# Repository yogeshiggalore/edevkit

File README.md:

# edevkit

> Open-source **embedded developer kits** for ARM + RISC-V work — one
> board on your desk that replaces a drawer full of dongles.

**edevkit** is a family of single-board USB-powered developer kits. Each
unit folds a debug probe, a stack of protocol testers, and a host
GUI / CLI into one device, so a developer working on an embedded board
can flash, debug, log, sniff, drive, emulate, and bring up new firmware
without keeping six other tools on the bench.

A single edevkit unit gives you, in one USB-C cable's worth of wiring:

- **ARM + RISC-V debug probe** — CMSIS-DAP v2 over USB, SWD + JTAG,
  works with pyOCD / OpenOCD / probe-rs / GDB
- **SWO trace capture** — ITM/TPIU output decoded and streamed to host
- **Two UART bridges** — one for the target's log console, one for
  developer-driven protocol testing (independent voltage domains)
- **I²C protocol tester** — master, slave, or sniffer at any address,
  up to 3.4 MHz
- **SPI / DSPI / QSPI tester** — master / slave / sniffer in every
  CPHA/CPOL mode, up to 50 MHz QSPI master
- **Device emulation engine** — YAML-driven; plays the role of a real
  SPI flash chip / I²C sensor / UART AT-modem so you can develop the
  *host* side without the actual peripheral on hand
- **OTA firmware updates** for the kit itself — MCUboot + SMP, no
  unplugging
- **Host stack** — a Tauri desktop GUI for visual inspection plus a
  Rust CLI for scripting and CI

The current product is **edevkit1**, in design (RP2350B Cortex-M33,
Zephyr 4.x, MCUboot). Future generations (`edevkit2`, …) will share
this same repo, toolchain, host stack, and docs hub — only the
hardware-specific design doc gets a version-numbered name.

---

## I'm new here — where do I start?

**Open the installation guide directly in your browser.** It's a
self-contained HTML page — no server, no build step, no setup required.

```bash
git clone https://github.com/yogeshiggalore/edevkit.git
cd edevkit

# macOS:
open tools/web/pages/installation.html

# Linux:
xdg-open tools/web/pages/installation.html

# Windows (PowerShell):
start tools/web/pages/installation.html
```

Or just double-click the file in your file manager. The same applies to
every other doc under `tools/web/pages/` — they're all standalone HTML
with embedded CSS, browseable via `file://` without any tooling.

The install guide walks you through (cross-platform):

1. System prerequisites (cmake, ninja, gperf, dtc, …)
2. Cloning the repo
3. Python venv + `west`
4. Zephyr workspace
5. Zephyr SDK
6. RP2350 PIO assembler
7. Rust + Tauri (host)
8. KiCad 9 + KiBot (hardware)
9. Enclosure CAD (CadQuery / FreeCAD)
10. Slicer (OrcaSlicer)
11. Bench tools (sigrok, mcumgr, serial)
12. Editor / IDE setup
13. Shell helpers
14. Smoke tests
15. Final checklist

Estimated total time: **1.5–3 hours** (mostly unattended downloads).

---

## I'm already set up — give me the docs hub

Once your venv is active, run the local docs hub for searchable
cross-referenced docs (light/dark theme, keyboard shortcuts, auto-discovers
new pages):

```bash
source "$EDEV_VENV/bin/activate"
cd tools/web
python server.py
# open http://127.0.0.1:8765/
```

The hub serves the same files you can already open via `file://` —
plus a searchable index, sidebar nav, and theme toggle.

---

## Repository layout

```
edevkit/
├── firmware/           Zephyr workspace + applications
│                       (per-product subdirs as the family grows)
├── hardware/           KiCad 9 schematic + PCB
├── host/               Rust workspace — Tauri GUI + CLI
├── enclosure/          CadQuery / FreeCAD source for 3D-printed shells
├── documents/          Non-HTML artifacts (PDFs, captures, diagrams)
└── tools/
    └── web/            Local docs hub (FastAPI)
        ├── pages/      ← all project HTML docs (open via file:// or hub)
        ├── server.py
        ├── static/     theme + JS
        └── templates/  Jinja2 templates
```

## Products

| Product   | Status     | Hardware                                  |
|-----------|------------|-------------------------------------------|
| edevkit1  | In design  | RP2350B (Cortex-M33) · Zephyr 4.x · MCUboot |

Future generations (edevkit2, …) will use this same repo, this same
toolchain, and these same docs hub conventions — only product-specific
content gets a version-numbered name.

## Documentation

All docs live under [`tools/web/pages/`](tools/web/pages/):

- [edevkit1 design spec](tools/web/pages/edevkit1.html) — v1 architecture (source of truth)
- [Installation guide](tools/web/pages/installation.html) — cross-platform onboarding

Drop any new `.html` into `tools/web/pages/` and it's immediately
discoverable by the docs hub (and openable via `file://`).

## Contributing

This is an open-hardware project: every contribution should be
reproducible from open-source tooling. No proprietary CAD, no
closed-source build steps. See the design spec's Decision Log section
for what's settled and what's still open.

## License

TBD.

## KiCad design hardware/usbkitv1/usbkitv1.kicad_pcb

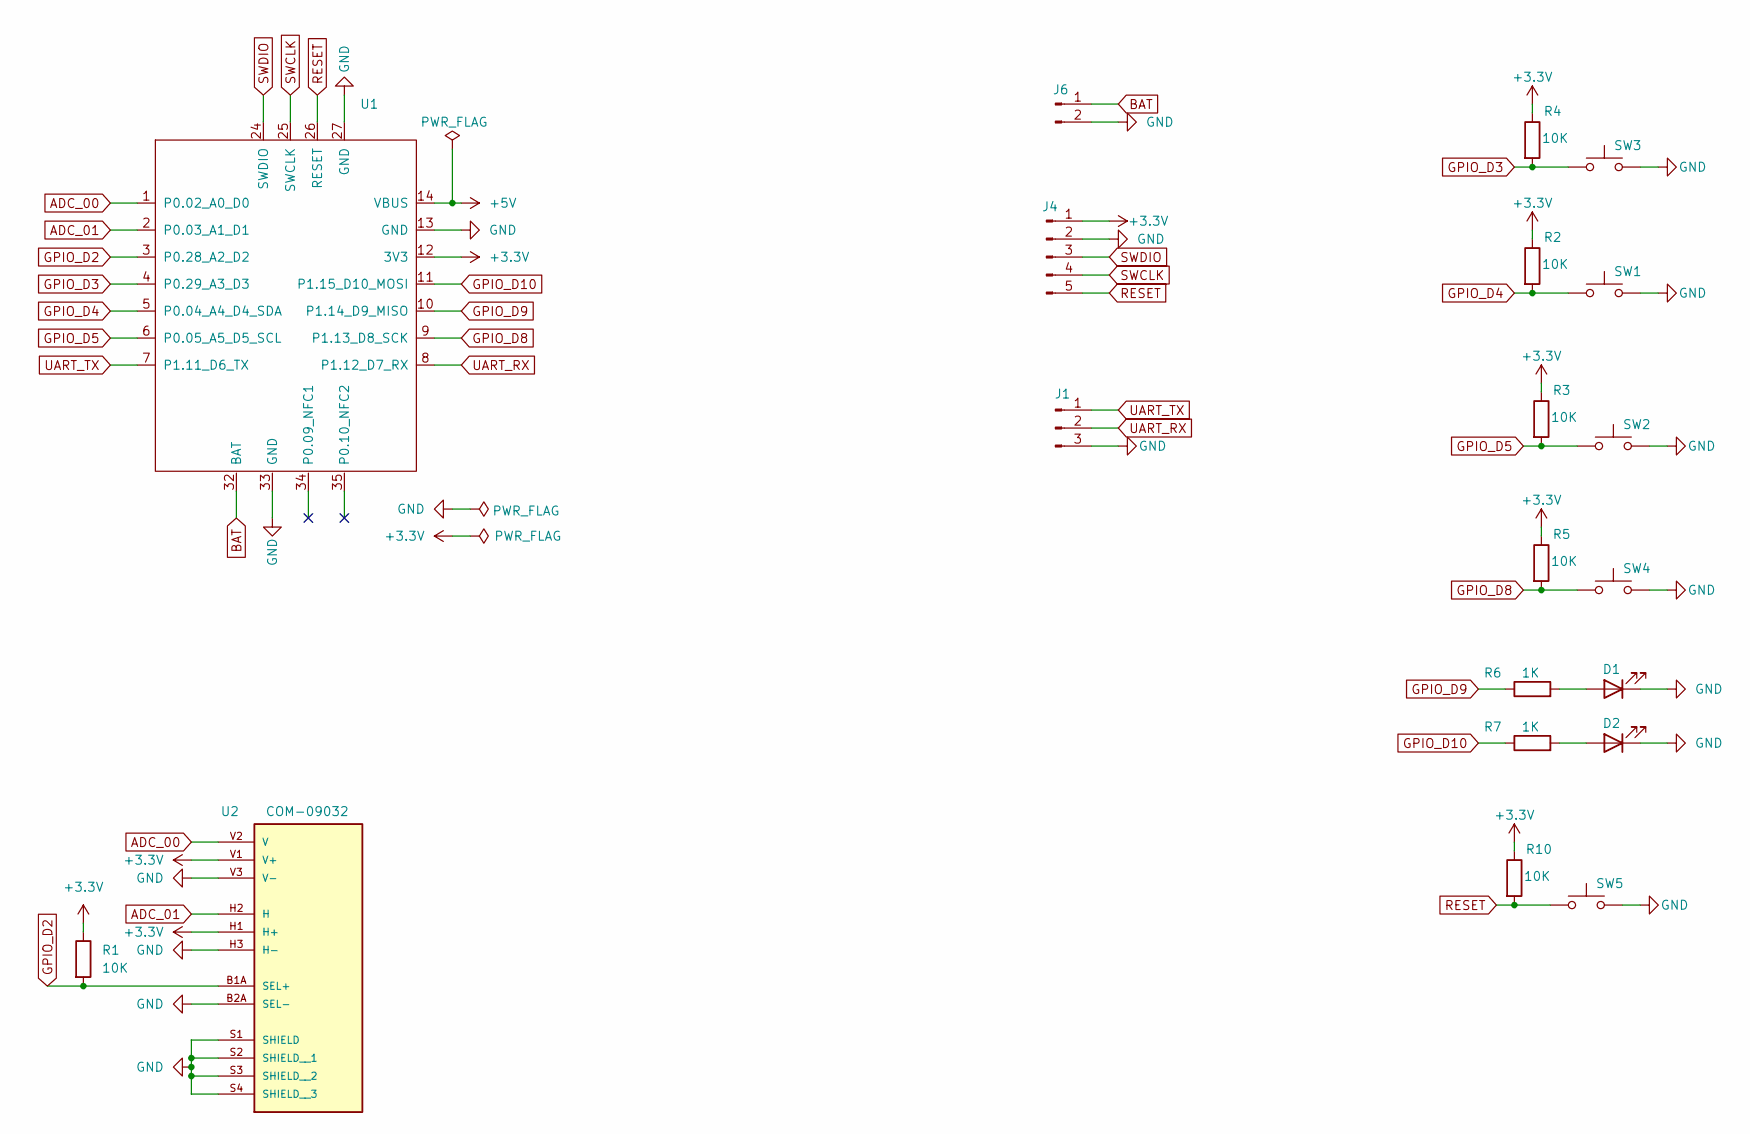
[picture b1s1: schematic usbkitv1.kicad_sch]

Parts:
D1, D2: LED; LED_0805_2012Metric_Pad1.15x1.40mm_HandSolder
J1: Conn_01x03_Pin; PinHeader_1x03_P2.54mm_Vertical
J4: Conn_01x05_Pin; PinHeader_1x05_P2.54mm_Vertical
J6: Conn_01x02_Pin; PinHeader_1x02_P2.54mm_Vertical
R1, R2, R3, R4, R5, R10: 10K; R_0805_2012Metric_Pad1.20x1.40mm_HandSolder
R6, R7: 1K; R_0805_2012Metric_Pad1.20x1.40mm_HandSolder
SW1, SW2, SW3, SW4: SW_Push; SW_PUSH-12mm
SW5: SW_Push; SW_PUSH_6mm
U1: XIAO-nRF52840-SMD
U2: COM-09032; XDCR_COM-09032; PARTREV N/A

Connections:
+3.3V: J4.1, R1.1, R2.1, R3.1, R4.1, R5.1, R10.1, U1.12 (3V3), U2.H1 (H+), U2.V1 (V+)
+5V: U1.14 (VBUS)
ADC_00: U1.1 (P0.02_A0_D0), U2.V2 (V)
ADC_01: U1.2 (P0.03_A1_D1), U2.H2 (H)
BAT: J6.1, U1.32 (BAT)
GND: D1.1 (K), D2.1 (K), J1.3, J4.2, J6.2, SW1.2, SW2.2, SW3.2, SW4.2, SW5.2, U1.13 (GND), U1.27 (GND), U1.33 (GND), U2.B2A (SEL-), U2.H3 (H-), U2.S1 (SHIELD), U2.S2 (SHIELD__1), U2.S3 (SHIELD__2), U2.S4 (SHIELD__3), U2.V3 (V-)
GPIO_D2: R1.2, U1.3 (P0.28_A2_D2), U2.B1A (SEL+)
GPIO_D3: R4.2, SW3.1, U1.4 (P0.29_A3_D3)
GPIO_D4: R2.2, SW1.1, U1.5 (P0.04_A4_D4_SDA)
GPIO_D5: R3.2, SW2.1, U1.6 (P0.05_A5_D5_SCL)
GPIO_D8: R5.2, SW4.1, U1.9 (P1.13_D8_SCK)
GPIO_D9: R6.1, U1.10 (P1.14_D9_MISO)
GPIO_D10: R7.1, U1.11 (P1.15_D10_MOSI)
unnamed: D1.2 (A), R6.2
unnamed: D2.2 (A), R7.2
RESET: J4.5, R10.2, SW5.1, U1.26 (RESET)
SWCLK: J4.4, U1.25 (SWCLK)
SWDIO: J4.3, U1.24 (SWDIO)
UART_RX: J1.2, U1.8 (P1.12_D7_RX)
UART_TX: J1.1, U1.7 (P1.11_D6_TX)

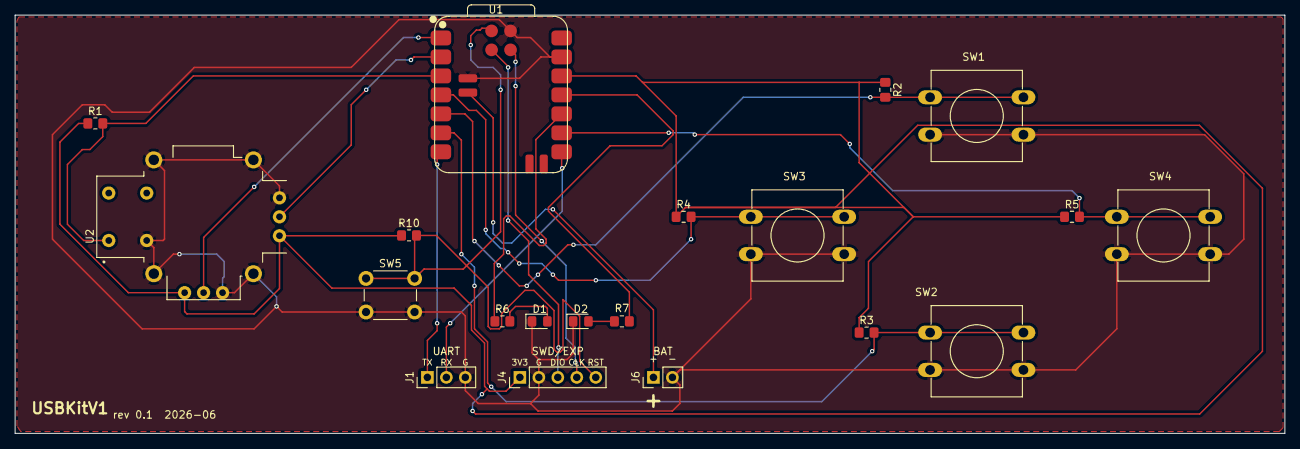
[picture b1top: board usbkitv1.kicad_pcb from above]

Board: 2 copper layers, 170.0 x 56.0 mm, 20 parts (0 on the bottom side), 19 nets.

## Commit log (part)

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2026-05-04 chore(docs): add Tailwind build tooling for the docs hub
    The docs hub at tools/web/ now uses Tailwind for ~95% of its styling.
    This commit lands the build setup so contributors can rebuild the CSS
    locally:
    - package.json: build:css / watch:css npm scripts
    - tailwind.config.js: brand palette, fonts, animations, content globs
    - tailwind.input.css: @tailwind directives + minimal custom layer
2026-05-04 feat(docs-hub): redesign hub — Tailwind, PWA, syntax highlight, search
    Rework tools/web/ from a hand-rolled CSS hub into a Tailwind-driven
    hub with full-text search, syntax highlighting, and offline support.
    Server (server.py):
    - Add 5 new categories — Architecture, USB stack, Debug, Protocols,
    Platform — slotted between Workflow and Bring-up so the chapter
    pages added in the next commit have homes
2026-05-04 docs: rewrite top-level README as the project's front door
    The previous README was a 2-line placeholder. Replace it with a
    proper landing page that introduces the edevkit family, summarizes
    what one unit does, and points new contributors to the docs hub.
    Highlights:
    - Frame "edevkit" as the umbrella brand and "edevkit1" as the
    current RP2350B product (consistent with the docs-hub naming)
2026-06-26 fix(edev_dapv2): nRF5340 flash via pyocd subprocess (Bug 2 — App side)
    probe-rs CMSIS-DAP flash silently fails on nRF5340: loader parses the HEX,
    exits without sending any flash transaction; misleading "TransferBlock
    USB timeout" message reported. Investigated via full RUST_LOG=trace —
    firmware ACKs every SWD transfer; the failure is host-side.
    Workaround: route nRF5340 hex through pyocd's FileProgrammer in a
    subprocess. Two issues blocked it:
2026-06-26 simplify(edev_dapv2 webgui): erase = wipe both cores + CTRL-AP reset
    The erase flow had grown three extra stages — UICR-disable stub upload,
    post-erase read-back verify, SYSRESETREQ-vs-CTRL-AP-reset switching for
    nRF5340 — that the user doesn't want. Strip them.
    Erase is now exactly:
    1. CTRL-AP#2 ERASEALL (App flash + App UICR)
    2. CTRL-AP#3 ERASEALL (Net flash + Net UICR, nRF5340 only)
2026-06-26 fix(edev_dapv2 webgui): pass --allow-erase-all on probe-rs read
    probe-rs reads a Nordic dual-core chip with a locked core hit
    "lacked the permission to do so: erase_all" because the auto-unlock
    path needs explicit permission. Trade-off documented at the call
    site: locked cores get auto-erased during read.
2026-06-26 feat(edev_dapv2 webgui): pyocd-based Net core flasher
    Direct host-driven Net flash via AP#1 + Net NVMC bridge, no on-target
    stub or SPU bootstrap needed:
    1. Defensive CTRL-AP#3 RESET pulse (clears any stuck-erase state from
    prior aborted ops)
    2. CTRL-AP#3 ERASEALL — wipes Net flash + Net UICR, unlocks Net AHB-AP
    for the rest of the session
2026-06-26 feat(edev_dapv2 webgui): J-Link CORESIGHT_Configure equivalent
    Ports nrfjprog's chip-recovery sequence into pure CMSIS-DAP. When the
    chip is in a stuck state — sticky CTRL/STAT errors, dormant DP, or a
    never-completing NVMC operation holding ERASEALLSTATUS at busy — our
    plain dp.connect() doesn't unstick it; J-Link does, and the magic
    turns out to live inside JLINK_CORESIGHT_Configure().
    New helper _full_dp_wake() runs the full ADIv5 §B5 init sequence via
2026-06-26 feat(edev_dapv2): permanent UICR.APPROTECT=HwDisabled after Net flash
    Hex files from production (Ring Pro 351) ship without UICR content.
    Without UICR.APPROTECT programmed to 0x50FA50FA (HwDisabled), the chip
    re-locks Net AHB-AP on every reset — so any post-reset readback verify
    returns garbage (the exact pattern we and nrfjprog both saw).
    Fix: after writing Net flash, while AHB-APs are still open from the
    CTRL-AP ERASEALL we did at the start of the session, program:
2026-06-26 fix(edev_dapv2 webgui): direct pyocd reads, no probe-rs auto-erase
    /api/read for nRF5340 was using probe-rs with --allow-erase-all.
    When ANY core was locked (typical post-reset state), probe-rs's
    Nordic vendor sequence would trigger a CTRL-AP ERASEALL — wiping
    BOTH cores, not just the locked one. Every readback verification
    was destroying the firmware we'd just programmed.
    Switch to direct pyocd AHB-AP reads for both App (AP#0, CSW=0x23000002)
2026-06-30 docs(esp32): add ESP32-S3 USB-host BLE bridge implementation guide
    The Pico 2 W stays as a pure USB CMSIS-DAP v2 probe; BLE moves to a
    separate ESP32-S3 firmware that hosts the probe over native USB-OTG
    and exposes its capabilities to a phone/fleet tool as semantic
    commands over BLE (NUS-style GATT + TLV framing).
    ESP32_BRIDGE.md is a complete implementation guide for that firmware
    — architecture, USB host code skeleton, NimBLE setup, TLV protocol,
2026-06-30 feat(edev_dapv2_zephyr): nRF5340 step 1 — DP/AP primitives + algorithm doc
    Lay the foundation for porting the canonical nRF5340 recover / erase /
    write / read flow from the pico-sdk Python webgui (feat/edev_dapv2 branch,
    algorithm-only reference) into the Zephyr probe firmware. The Pico runs
    the multi-step CTRL-AP / NVMC / UICR / stub-upload sequence itself; host
    orchestration becomes thin (one DAP vendor command per high-level op).
    Adds:
2026-06-30 feat(edev_dapv2_zephyr): nRF5340 step 3 — App UICR programming (cmd 0x8A)
    Implements the host-side App UICR.APPROTECT / SECUREAPPROTECT
    programming flow — no on-target stub needed because the App core's
    secure context is set up by silicon defaults. Net core UICR needs the
    SPU bootstrap stub (step 4). Algorithm: docs/NRF5340_ALGORITHMS.md §4
    Stage 3.
    Adds:
2026-06-30 feat(edev_dapv2_zephyr): nRF5340 step 4 — Net stub + UICR programming (cmd 0x8B)
    Implements the on-target Net-core stub path for permanently disabling
    APPROTECT on the network core. Required because nRF5340 Net peripherals
    are "Selectable Secure" and bare Secure-mode AHB-AP writes fault until
    the SPU is configured — sidestepped by running the programming code on
    the Net CPU itself, where silicon defaults give us the secure context
    we need. Algorithm: docs/NRF5340_ALGORITHMS.md §4 Stages 4–8 + §7.
2026-06-30 release(edev_dapv2_zephyr): v0.1-step5 — RECOVER + ERASE + UICR ops
    First release candidate of the Zephyr port for the edev_dapv2 firmware
    with Nordic chip recovery primitives. Tip commit:
    652b9cc feat(edev_dapv2_zephyr): nRF5340 step 5 — NRF53_RECOVER (cmd 0x84)
    What's in the release:
    releases/v0.1-step5/RELEASE.md — full release notes: vendor
    command surface, wire format, how
2026-06-30 docs(esp32): align ESP32_BRIDGE.md with v0.1-step5 Pico release
    The ESP32 bridge author hit a real conflict: Appendix G.3 listed
    pico-sdk legacy vendor commands (CORTEX_M_HALT 0x80, NRF_RESET 0x83,
    CORTEX_M_DUMP 0x8A, SWCLK_KEEPALIVE 0x90/0x91) that the Zephyr port
    does not implement. Worse, 0x8A was double-claimed — the doc said
    CORTEX_M_DUMP, the Zephyr firmware says NRF53_UICR_PROGRAM_APP. An
    ESP32 implementation following the older doc would silently hit
2026-06-30 test(edev_dapv2_zephyr): chip-aware harness — nRF52840 + nRF5340 paths
    Refactor test_nrf53_vendor_cmds.py to gate nRF5340-only tests off chip
    detection. Add a basic SWD link check ("ping") via standard CMSIS-DAP
    and a post-erase verification ("verify-erase") that reads flash[0]
    through AHB-AP to confirm the wipe took.
    Suite order (auto mode):
    1. ping — DAP_Connect + line reset + DPIDR + AP[0].IDR
2026-06-30 release(edev_dapv2_zephyr): v0.1.1-step5 — nRF52840 hardware-validated
    Bug-fix release of v0.1-step5 with three dp_full_wake fixes that make
    nRF52840 actually work (commit fa5d305). Plus a chip-aware test harness
    that ran 5/5 PASS against a bench nRF52840.
    Adds:
    releases/v0.1.1-step5/RELEASE.md — full release notes including a
    per-chip support matrix (nRF52840
2026-06-30 feat(edev_dapv2_zephyr): step 8 — NRF53_READ_MEM + Net stub DP-wake fix
    Adds vendor cmd 0x88 NRF53_READ_MEM — chip-agnostic AHB-AP burst read.
    Works on nRF52840 + nRF5340 + any ARM Cortex-M target reachable via
    AHB-AP. Optional VC_CORERESET-clear flag for the nRF5340 App-readback-
    0xFF fix (Bug 6a). Wire format documented in nrf53_vendor.c.
    Also includes the post-CTRL-AP#3-RESET full_dp_wake refresh in
    nrf53_uicr_program_net — matches the Python reference's stage 7
2026-06-30 docs(release): point v0.1.1-step5 RELEASE.md at v0.1.2-step8 successor
2026-06-30 feat(edev_dapv2_zephyr): v0.1.3-step8 — NRF53_WRITE_MEM (0x8C)
    Counterpart to 0x88 READ_MEM. Chip-agnostic AHB-AP burst write —
    replaces multi-DAP_Transfer (CSW+TAR+DRW) sequences with one packet.
    nrf53_write_mem() — per-word AHB-AP write loop with
    sticky-clear at entry, no auto-inc
    (Nordic 1-KB TAR-wrap workaround)
    vendor 0x8C dispatch — request format mirror of 0x88 plus
2026-06-30 feat(edev_dapv2_zephyr): v0.1.5-step6 — NRF53_FLASH_WRITE_NET (0x86)
    Step 6 of the 10-step plan ships. Probe-side batched Net flash
    programming: write up to 14 contiguous 32-bit words per packet, with
    the NVMC sequence (Wen → per-word write+READY → Ren) all wrapped
    inside the probe.
    nrf53_flash_write_net() — orchestrates Net NVMC: sticky-clear,
    enter Wen, per-word write+wait READY,
2026-06-30 feat(edev_dapv2_zephyr): v0.1.6-step7 — NRF53_FLASH_WRITE_APP (0x87)
    Step 7 of the 10-step plan ships. App-flash counterpart of 0x86,
    shipped in v0.1.5. Mirrors the NVMC programming dance for the App
    AHB-AP, family-aware via the nvmc_base parameter:
    - nRF52840 / 833 / 832: nvmc_base = 0x4001E000
    - nRF5340 App: nvmc_base = 0x50039000
    nrf53_flash_write_app(nvmc_base, addr, n, data, &written)
2026-06-30 feat(edev_dapv2_zephyr): v0.1.7 — NRF53_TARGET_INFO (0x89)
    Final planned vendor command. Returns DPIDR + AP[0].IDR + CPUID in
    one 14-byte response — replaces three round-trips with one.
    nrf53_target_info() — full_dp_wake to get DPIDR (mandatory
    first xact after line reset), then
    AP[0].IDR via standard AP read, then
    CPUID at 0xE000ED00 via App AHB-AP
2026-06-30 docs(esp32): v0.1.7 sync — 0x89 TARGET_INFO + FICR caveat
    The bridge author hits the same FICR-reads-0xFFFFFFFF trap I did on
    nRF5340 DK silicon. Documenting the caveat in K.4 with a recommendation
    to use 0x89 for family detection + targeted 0x88 probes for subtype.
    Updates:
    - "Pico-side firmware status" callout: v0.1.6-step7 → v0.1.7
    (tip dcf721c → 31e3082); bench-acceptance line updated to 11/11.
2026-06-30 docs+tools: document Net flash @ 0x01000000 write gotcha (bench-verified)
    While running the canonical info→read→erase→recover→write
    sequence on bench nRF5340 DK, found that writes to the very
    first word of Net flash (0x01000000) silently succeed at the
    NVMC level (probe reports 14/14 words_written, status=OK) but
    the value does NOT appear on readback. Data at 0x01000000 ends
    up looking like remnants of the Net stub vector table.
2026-06-30 release: v0.1.8 — docs+tools (firmware byte-identical to v0.1.7)
    Cuts a v0.1.8 release packaging everything that's landed since
    v0.1.7 (commits 79c9bc2, 065803e, c26fbfa). No firmware source
    has changed — the v0.1.7 zephyr.uf2/bin/elf binaries are reused
    verbatim (same SHA256s). A v0.1.7 probe IS a v0.1.8 probe; users
    do NOT need to re-flash.
    Release artifacts:
